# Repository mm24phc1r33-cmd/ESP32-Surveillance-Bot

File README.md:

# ESP32-Surveillance-Bot
#  ESP32-Based Smart Surveillance Robot (Embedded Systems Project)

##  Overview

This project presents the design and development of an ESP32-based smart robotic system capable of motion control, laser aiming, video streaming, GPS tracking, and secure communication. The system integrates multiple hardware modules with embedded firmware to create a scalable and real-time surveillance platform.

The robot operates using differential drive motors, supports remote monitoring via Wi-Fi, and ensures secure access using BLE authentication.

---

##  Objectives

The main objective of this project is to design a complete embedded system including:

* Real-time motor control using PWM
* Laser aiming using servo motor
* GPS-based location tracking
* Wireless communication via Wi-Fi
* Secure access using BLE authentication
* Camera-based monitoring (simulated/extendable)

---

##  System Architecture

The system consists of the following major blocks:

* ESP32 microcontroller (central controller)
* Motor driver (TB6612FNG)
* DC motors for movement
* Servo motor for laser aiming
* GPS module (UART-based)
* Wi-Fi communication module (ESP32 inbuilt)
* BLE authentication system
* Power regulation using AMS1117

---

##  Hardware Components

* ESP32-WROOM-32
* TB6612FNG Motor Driver
* 2 × DC Motors
* 1 × Servo Motor
* GPS Module (NEO-6M or similar)
* AMS1117 Voltage Regulator (3.3V)
* Capacitors (10µF)
* Resistors (220Ω, 10kΩ)
* Push Buttons (Reset & Boot)
* LED Indicator
* Connectors (Pin Headers & Terminal Blocks)

---

##  PCB Design

A custom PCB was designed using KiCad with the following considerations:

* Proper component placement (power, control, communication separation)
* Wide traces for motor power lines
* Ground plane for noise reduction
* Keep-out zone for ESP32 antenna
* Decoupling capacitors near power pins
* Separate connectors for GPS, UART, motors, and servo

---

##  Firmware Features

The firmware is developed using Arduino IDE for ESP32 and includes:

* Motor control (forward, backward, left, right)
* PWM-based speed control
* Servo control for laser positioning
* GPS data parsing (latitude & longitude)
* Wi-Fi connectivity and server communication
* BLE-based authentication (simulated)
* Safety mechanism (motor stop on disconnection)

---

##  Communication

* Wi-Fi: Used for data transmission and remote monitoring
* BLE: Used for authentication before granting control
* UART: Used for GPS communication

---

##  Testing & Output

The system was tested using Serial Monitor:

* Verified motor control commands
* GPS data updated every 5 seconds
* Simulated authentication process
* Safety stop triggered on connection loss

---

##  Safety Features

* Motors automatically stop on Wi-Fi disconnect
* Controlled access using BLE authentication
* Power regulation to avoid voltage fluctuations

---

##  Project Structure

```
ESP32_Surveillance_Bot/
│── firmware/
│   └── main.ino
│
│── hardware/
│   ├── schematic.kicad_sch
│   ├── pcb_layout.kicad_pcb
│   ├── gerber_files/
│
│── README.md
```

---

##  Future Improvements

* Real-time camera streaming using ESP32-CAM
* Mobile app integration
* Autonomous navigation using sensors
* AI-based object detection

---

##  Conclusion

This project demonstrates the integration of embedded systems, PCB design, and communication protocols into a single functional robotic platform. It showcases practical implementation skills in hardware-software co-design and real-time system development.

---

## Author

**Monika**
M.Sc. Tech Engineering Physics (Electronics)
NIT Warangal

---

## 🔗 GitHub

[(Add your GitHub repo link here)](https://github.com/mm24phc1r33-cmd/ESP32-Surveillance-Bot)

---

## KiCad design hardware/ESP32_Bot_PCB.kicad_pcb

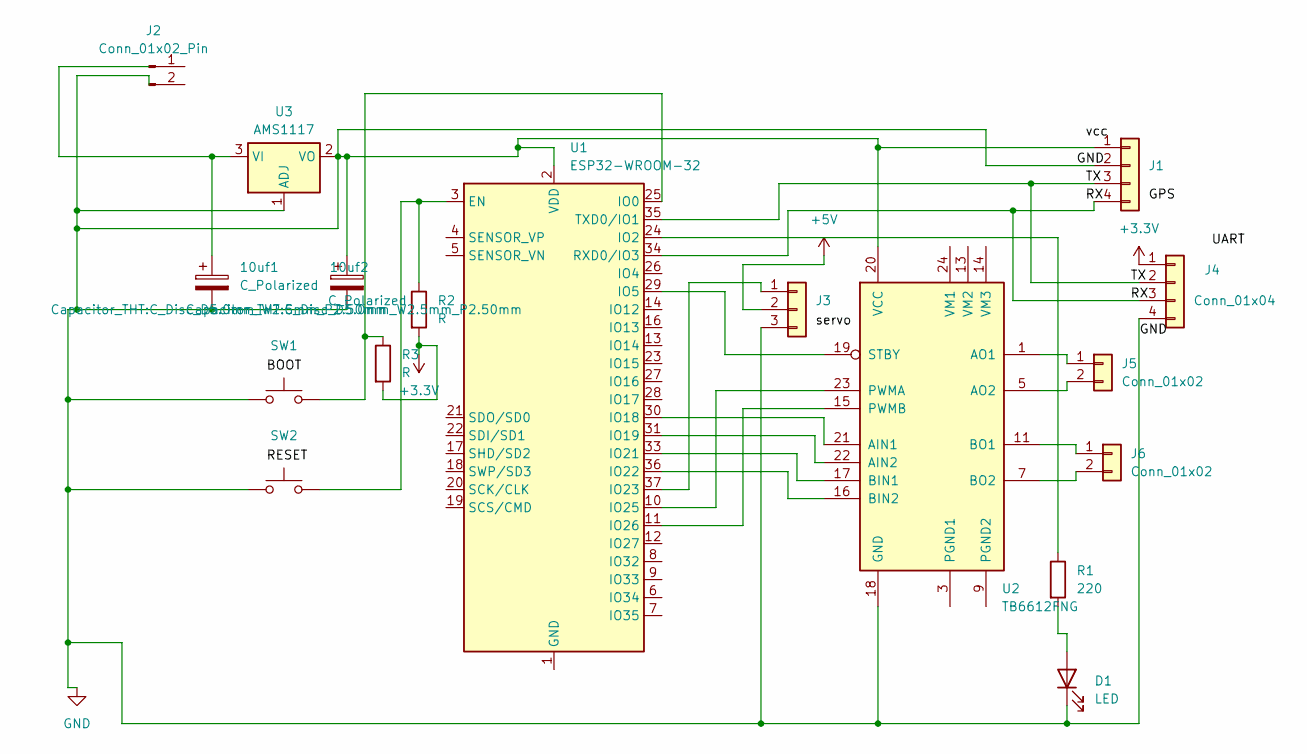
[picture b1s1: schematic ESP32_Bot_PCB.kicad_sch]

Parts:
10uf1, 10uf2: C_Polarized; C_Disc_D5.0mm_W2.5mm_P2.50mm
D1: LED; LED_D5.0mm
J1, J4: Conn_01x04; PinHeader_1x04_P2.54mm_Vertical
J2: Conn_01x02_Pin; TerminalBlock_MaiXu_MX126-5.0-02P_1x02_P5.00mm
J3: Conn_01x03; PinHeader_1x03_P2.54mm_Vertical
J5, J6: Conn_01x02; TerminalBlock_MaiXu_MX126-5.0-02P_1x02_P5.00mm
R1: 220; R_Axial_DIN0207_L6.3mm_D2.5mm_P7.62mm_Horizontal
R2, R3: R; R_Axial_DIN0207_L6.3mm_D2.5mm_P7.62mm_Horizontal
SW1, SW2: SW_Push; SW_PUSH_6mm
U1: ESP32-WROOM-32
U2: TB6612FNG; SSOP-24_5.3x8.2mm_P0.65mm
U3: AMS1117; SOT-223-3_TabPin2

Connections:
+3.3V: J4.1, R2.2, R3.2
+5V: J3.2
/RX: J1.4, J4.3, U1.34 (RXD0/IO3)
/TX: J1.3, J4.2, U1.35 (TXD0/IO1)
GND: 10uf1.2, 10uf2.1, 10uf2.2, D1.1 (K), J1.1, J1.2, J3.3, J4.4, SW1.1, SW2.1, U1.2 (VDD), U2.18 (GND), U2.20 (VCC), U3.1 (ADJ), U3.2 (VO)
unnamed: D1.2 (A), R1.2
unnamed: J3.1, U1.37 (IO23)
unnamed: J5.1, U2.1 (AO1), U2.2 (AO1)
unnamed: J5.2, U2.5 (AO2), U2.6 (AO2)
unnamed: J6.1, U2.11 (BO1), U2.12 (BO1)
unnamed: J6.2, U2.7 (BO2), U2.8 (BO2)
unnamed: R2.1, SW2.2, U1.3 (EN)
unnamed: U1.1 (GND), U1.15 (GND), U1.38 (GND), U1.39 (GND)
unnamed: R3.1, SW1.2, U1.25 (IO0)
unnamed: R1.1, U1.24 (IO2)
unnamed: U1.29 (IO5), U2.19 (STBY)
unnamed: U1.30 (IO18), U2.21 (AIN1)
unnamed: U1.31 (IO19), U2.22 (AIN2)
unnamed: U1.33 (IO21), U2.17 (BIN1)
unnamed: U1.36 (IO22), U2.16 (BIN2)
unnamed: U1.10 (IO25), U2.23 (PWMA)
unnamed: U1.11 (IO26), U2.15 (PWMB)
unnamed: U2.3 (PGND1), U2.4 (PGND1)
unnamed: U2.9 (PGND2), U2.10 (PGND2)
unnamed: 10uf1.1, U3.3 (VI)

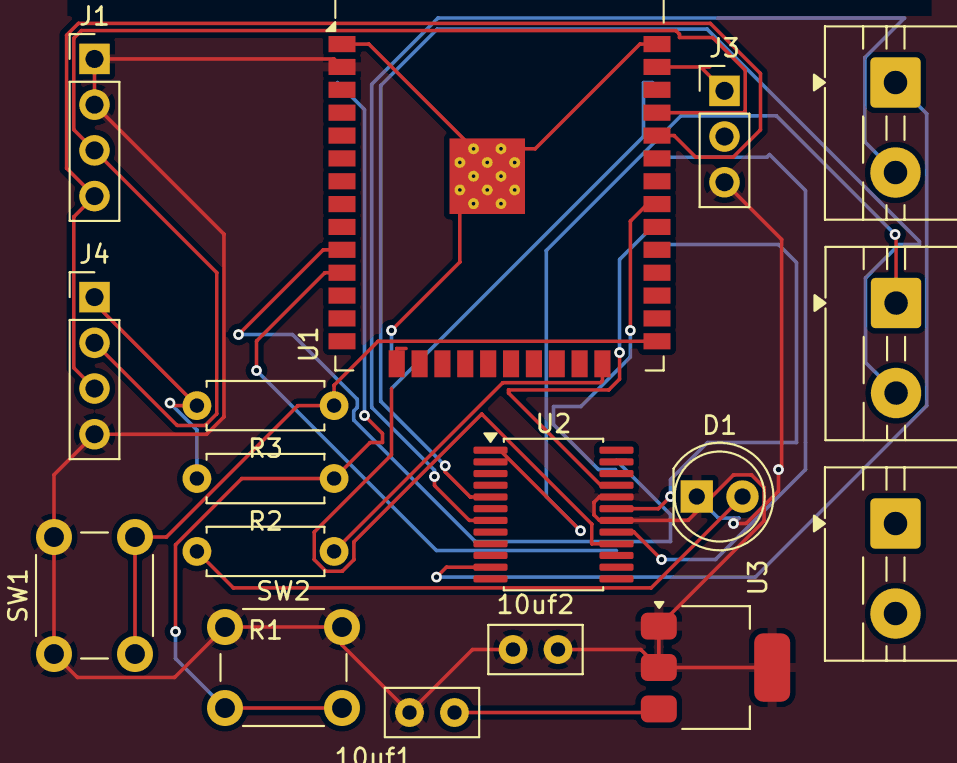
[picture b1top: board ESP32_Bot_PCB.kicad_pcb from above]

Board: 2 copper layers, 17 parts (0 on the bottom side), 24 nets.

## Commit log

2026-04-09 Create screenshorts
2026-04-09 Update screenshorts
